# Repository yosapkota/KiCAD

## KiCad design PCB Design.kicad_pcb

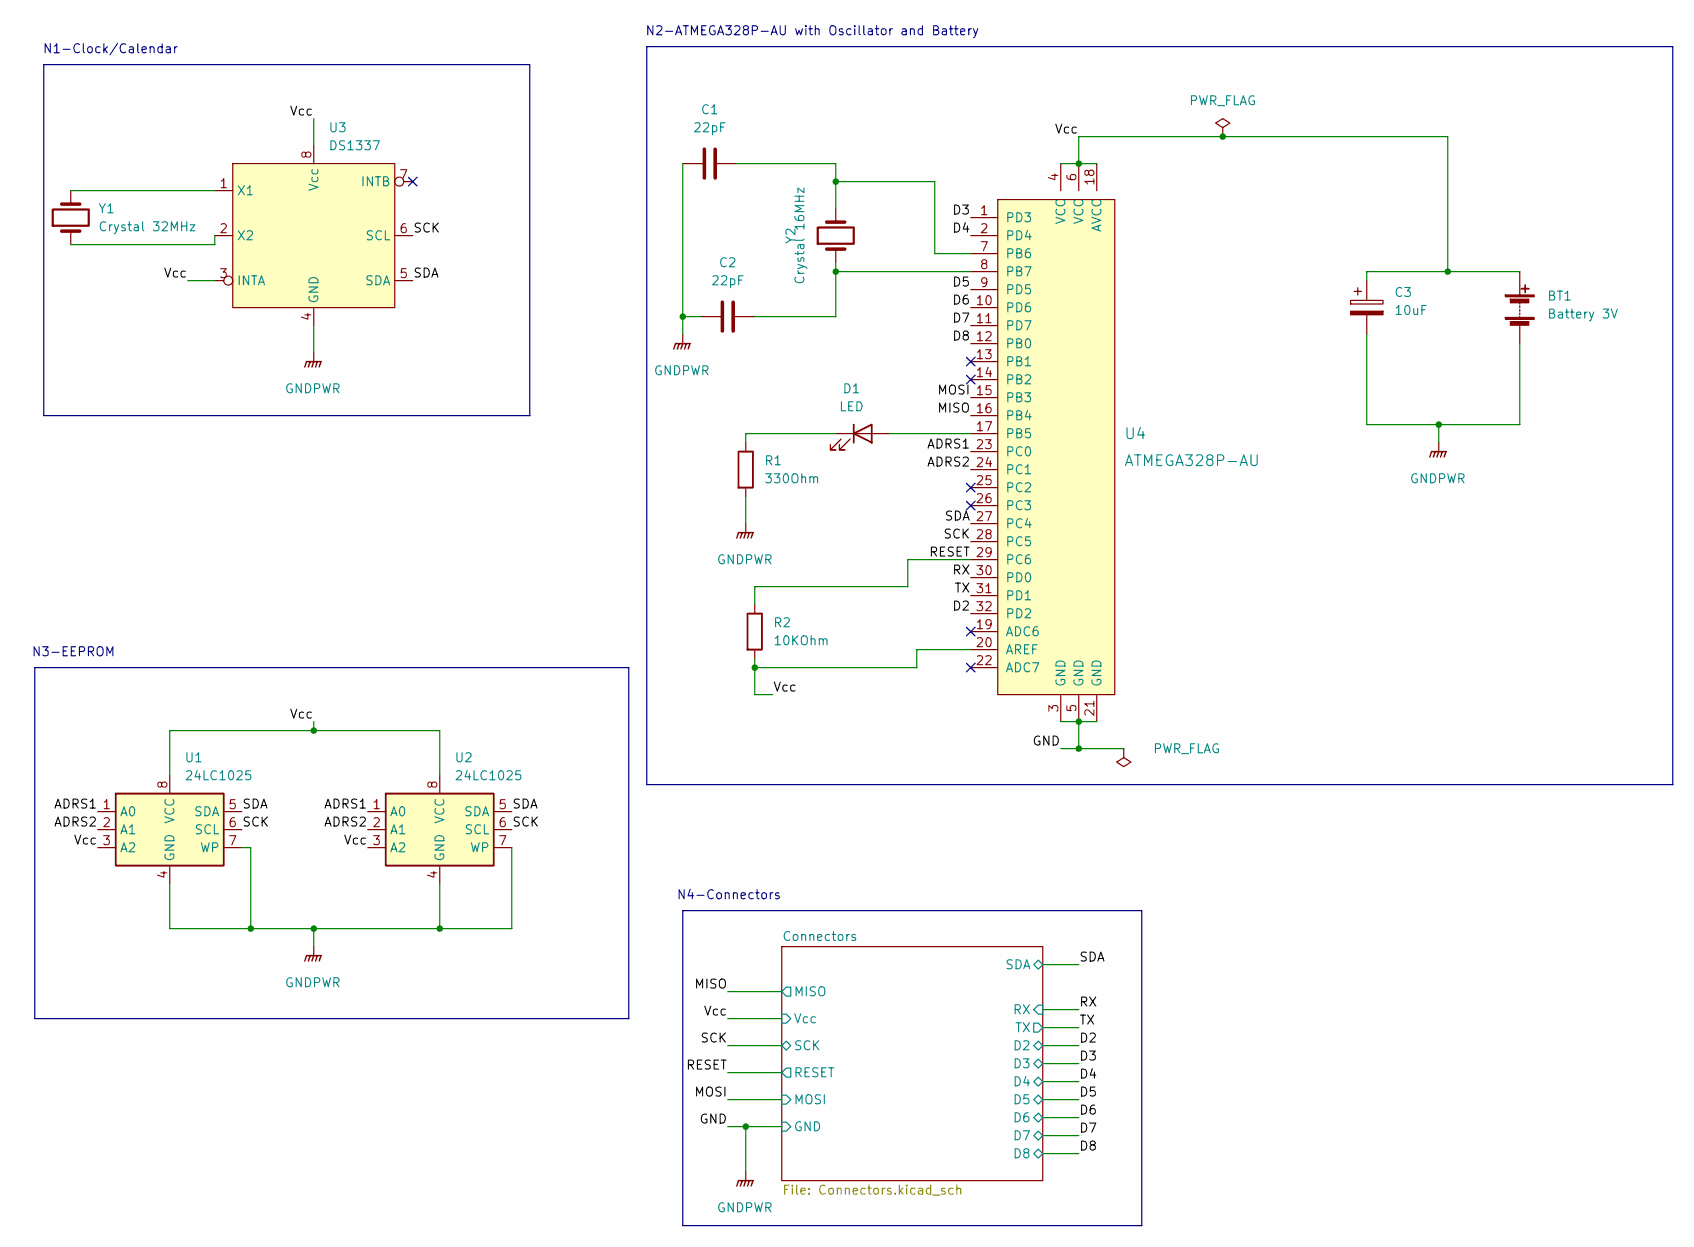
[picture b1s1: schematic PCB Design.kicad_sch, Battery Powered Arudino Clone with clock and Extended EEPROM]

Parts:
BT1: Battery 3V; PinHeader_1x02_P2.54mm_Vertical
C1, C2: 22pF; C_0805_2012Metric_Pad1.18x1.45mm_HandSolder
C3: 10uF; C_0805_2012Metric_Pad1.18x1.45mm_HandSolder
D1: LED; LED_0805_2012Metric_Pad1.15x1.40mm_HandSolder
R1: 330Ohm; R_0805_2012Metric_Pad1.20x1.40mm_HandSolder
R2: 10KOhm; R_0805_2012Metric_Pad1.20x1.40mm_HandSolder
U1, U2: 24LC1025; SOIC-8_5.23x5.23mm_P1.27mm
U3: DS1337; SO-8_5.3x6.2mm_P1.27mm
U4: ATMEGA328P-AU; TQFP-32_7x7mm; MPN ATMEGA328P-AU; Digi-Key_PN ATMEGA328P-AU-ND
Y1: Crystal 32MHz; Crystal_SMD_MicroCrystal_CC7V-T1A-2Pin_3.2x1.5mm
Y2: Crystal 16MHz; Crystal_SMD_5032-2Pin_5.0x3.2mm_HandSoldering

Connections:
/ADRS1: U1.1 (A0), U2.1 (A0), U4.23 (PC0)
/ADRS2: U1.2 (A1), U2.2 (A1), U4.24 (PC1)
/D2: U4.32 (PD2); also elsewhere on the board
/D3: U4.1 (PD3); also elsewhere on the board
/D4: U4.2 (PD4); also elsewhere on the board
/D5: U4.9 (PD5); also elsewhere on the board
/D6: U4.10 (PD6); also elsewhere on the board
/D7: U4.11 (PD7); also elsewhere on the board
/D8: U4.12 (PB0); also elsewhere on the board
/MISO: U4.16 (PB4); also elsewhere on the board
/MOSI: U4.15 (PB3); also elsewhere on the board
/RESET: R2.1, U4.29 (PC6); also elsewhere on the board
/RX: U4.30 (PD0); also elsewhere on the board
/SCK: U1.6 (SCL), U2.6 (SCL), U3.6 (SCL), U4.28 (PC5); also elsewhere on the board
/SDA: U1.5 (SDA), U2.5 (SDA), U3.5 (SDA), U4.27 (PC4); also elsewhere on the board
/TX: U4.31 (PD1); also elsewhere on the board
/Vcc: BT1.1 (+), C3.1, R2.2, U1.3 (A2), U1.8 (VCC), U2.3 (A2), U2.8 (VCC), U3.3 (INTA), U3.8 (Vcc), U4.4 (VCC), U4.6 (VCC), U4.18 (AVCC), U4.20 (AREF); also elsewhere on the board
GNDPWR: BT1.2 (-), C1.1, C2.1, C3.2, R1.2, U1.4 (GND), U1.7 (WP), U2.4 (GND), U2.7 (WP), U3.4 (GND), U4.3 (GND), U4.5 (GND), U4.21 (GND); also elsewhere on the board
unnamed: D1.1 (K), R1.1
unnamed: U3.1 (X1), Y1.2
unnamed: U3.2 (X2), Y1.1
unnamed: C1.2, U4.7 (PB6), Y2.2
unnamed: C2.2, U4.8 (PB7), Y2.1
unnamed: D1.2 (A), U4.17 (PB5)

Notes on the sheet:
N3-EEPROM
N2-ATMEGA328P-AU with Oscillator and Battery
N1-Clock/Calendar
N4-Connectors

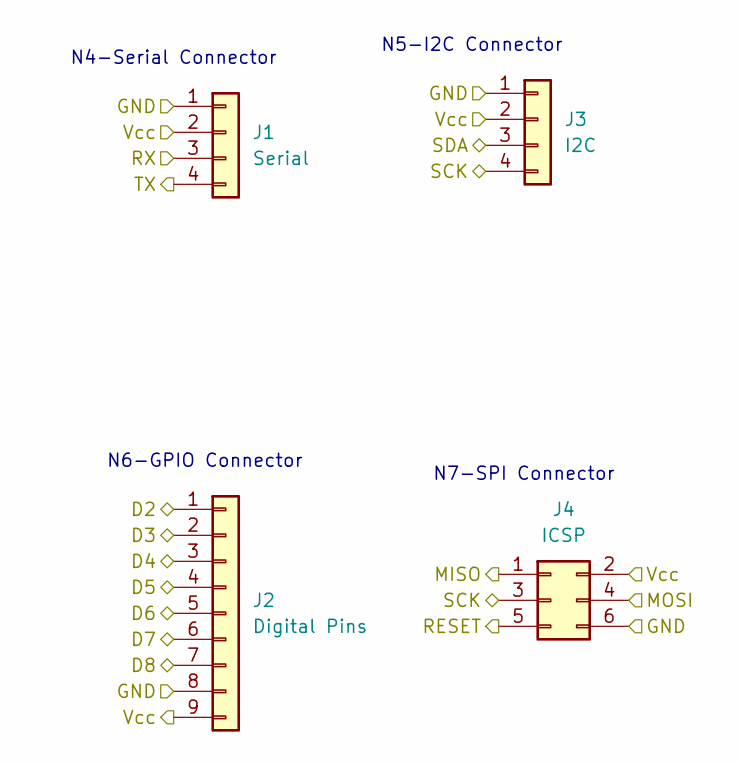
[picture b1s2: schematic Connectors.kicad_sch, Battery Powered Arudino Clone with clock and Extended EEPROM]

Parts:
J1: Serial; PinSocket_1x04_P2.54mm_Vertical
J2: Digital Pins; PinSocket_1x09_P2.54mm_Vertical
J3: I2C; PinSocket_1x04_P2.54mm_Vertical
J4: ICSP; PinSocket_2x03_P2.54mm_Vertical

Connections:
/D2: J2.1; also elsewhere on the board
/D3: J2.2; also elsewhere on the board
/D4: J2.3; also elsewhere on the board
/D5: J2.4; also elsewhere on the board
/D6: J2.5; also elsewhere on the board
/D7: J2.6; also elsewhere on the board
/D8: J2.7; also elsewhere on the board
/MISO: J4.1; also elsewhere on the board
/MOSI: J4.4; also elsewhere on the board
/RESET: J4.5; also elsewhere on the board
/RX: J1.3; also elsewhere on the board
/SCK: J3.4, J4.3; also elsewhere on the board
/SDA: J3.3; also elsewhere on the board
/TX: J1.4; also elsewhere on the board
/Vcc: J1.2, J2.9, J3.2, J4.2; also elsewhere on the board
GNDPWR: J1.1, J2.8, J3.1, J4.6; also elsewhere on the board

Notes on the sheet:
N4-Serial Connector
N6-GPIO Connector
N5-I2C Connector
N7-SPI Connector

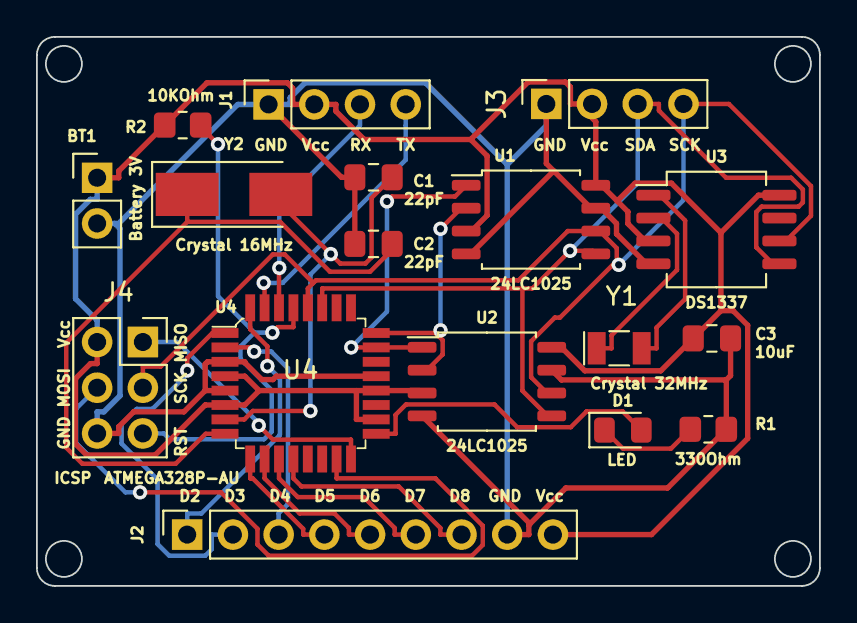
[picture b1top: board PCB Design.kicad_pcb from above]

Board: 2 copper layers, 43.5 x 30.5 mm, 17 parts (0 on the bottom side), 24 nets.

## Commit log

2022-06-04 added symbols and created a child sheet
2022-06-04 add ATMEGA328P-AU from Digi-key library
2022-06-04 add custom clock IC symbol
2022-06-04 complete footprint association
2022-06-05 complete wiring in the root sheet
2022-06-05 add functional block description
2022-06-05 first iteration of layout
2022-06-05 add outline and mounting holes
2022-06-05 finish routing 2 layer board with freerouting
2022-06-05 finish routing 4 layer board
2022-06-05 add copper fill in 2 layered board
2022-06-05 generate Gerber files and BOM
2022-06-05 generate BOM for assembly and pick & place
2022-11-19 remove redundant gerber files
